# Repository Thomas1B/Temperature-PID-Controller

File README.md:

# Temperature PID Controller using an Arduino

This project uses a PID controller algorithm to heat up a heating cartridge and maintain an accurate temperature using an Arduino nano.
<br><br>

<br>

## Schematic

<br>

## Parts List

See `Parts_list.csv`

## Controls

1. Single-press to reset set temperature.
2. Double-press increase increment step for changing set temperature.
3. Press & hold to start up heating process.

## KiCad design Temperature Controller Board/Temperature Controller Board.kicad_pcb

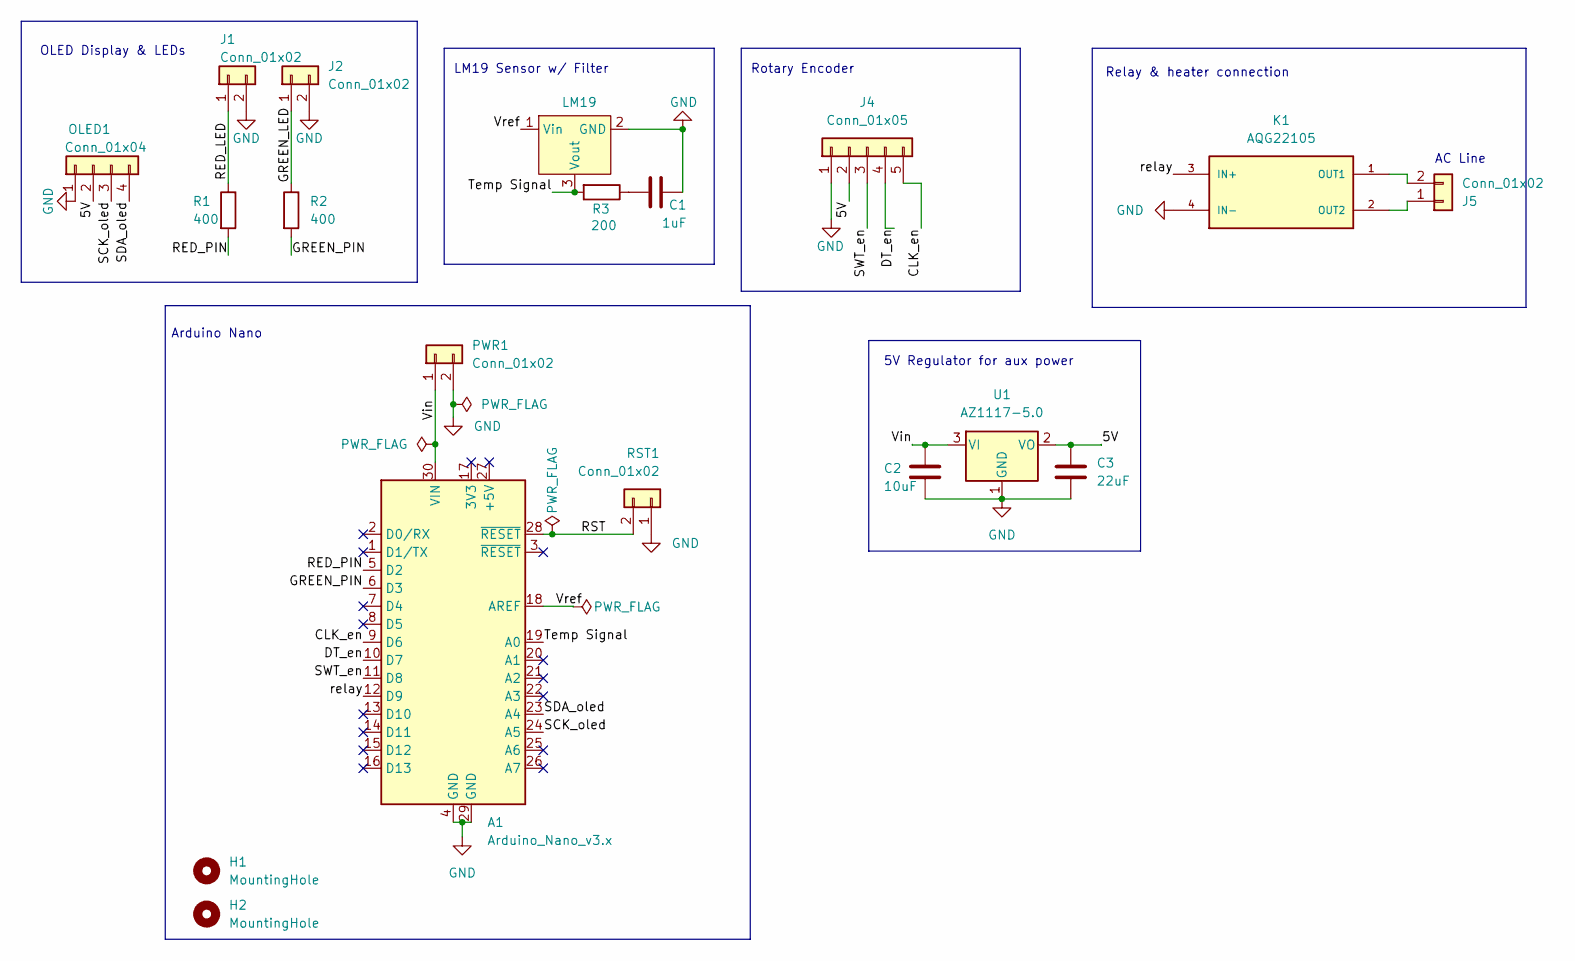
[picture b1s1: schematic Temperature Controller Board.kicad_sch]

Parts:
A1: Arduino_Nano_v3.x; Arduino Riser
C1: 1uF; C_0805_2012Metric_Pad1.18x1.45mm_HandSolder
C2: 10uF; C_0805_2012Metric_Pad1.18x1.45mm_HandSolder
C3: 22uF; C_0805_2012Metric_Pad1.18x1.45mm_HandSolder
H1, H2: MountingHole; MountingHole_3.2mm_M3
J1, J2: Conn_01x02; JST_XH_B2B-XH-A_1x02_P2.50mm_Vertical
J4: Conn_01x05; JST_XH_B5B-XH-A_1x05_P2.50mm_Vertical
J5: Conn_01x02; myTerminalBlock-2_P5.08mm
K1: AQG22105; RELAY_AQG22105
LM19: LM19; JST_XH_B3B-XH-AM_1x03_P2.50mm_Vertical
OLED1: Conn_01x04; JST_XH_B4B-XH-A_1x04_P2.50mm_Vertical
PWR1: Conn_01x02; JST_XH_B2B-XH-A_1x02_P2.50mm_Vertical
R1, R2: 400; R_0805_2012Metric_Pad1.20x1.40mm_HandSolder
R3: 200; R_0805_2012Metric_Pad1.20x1.40mm_HandSolder
RST1: Conn_01x02; JST_XH_B2B-XH-A_1x02_P2.50mm_Vertical
U1: AZ1117-5.0; SOT-223-3_TabPin2

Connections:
/5V: C3.1, J4.2, OLED1.2, U1.2 (VO)
/CLK_en: A1.9 (D6), J4.5
/DT_en: A1.10 (D7), J4.4
/GREEN_LED: J2.1, R2.1
/GREEN_PIN: A1.6 (D3), R2.2
/RED_LED: J1.1, R1.1
/RED_PIN: A1.5 (D2), R1.2
/RST: A1.28 (~RESET), RST1.2
/SCK_oled: A1.24 (A5), OLED1.3
/SDA_oled: A1.23 (A4), OLED1.4
/SWT_en: A1.11 (D8), J4.3
/Temp Signal: A1.19 (A0), LM19.3 (Vout), R3.2
/Vin: A1.30 (VIN), C2.1, PWR1.1, U1.3 (VI)
/Vref: A1.18 (AREF), LM19.1 (Vin)
/relay: A1.12 (D9), K1.3 (IN+)
GND: A1.4 (GND), A1.29 (GND), C1.1, C2.2, C3.2, J1.2, J2.2, J4.1, K1.4 (IN-), LM19.2 (GND), OLED1.1, PWR1.2, RST1.1, U1.1 (GND)
unnamed: C1.2, R3.1
unnamed: J5.1, K1.2 (OUT2)
unnamed: J5.2, K1.1 (OUT1)

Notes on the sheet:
Arduino Nano
5V Regulator for aux power
OLED Display & LEDs
AC Line
Rotary Encoder
Relay & heater connection
LM19 Sensor w/ Filter

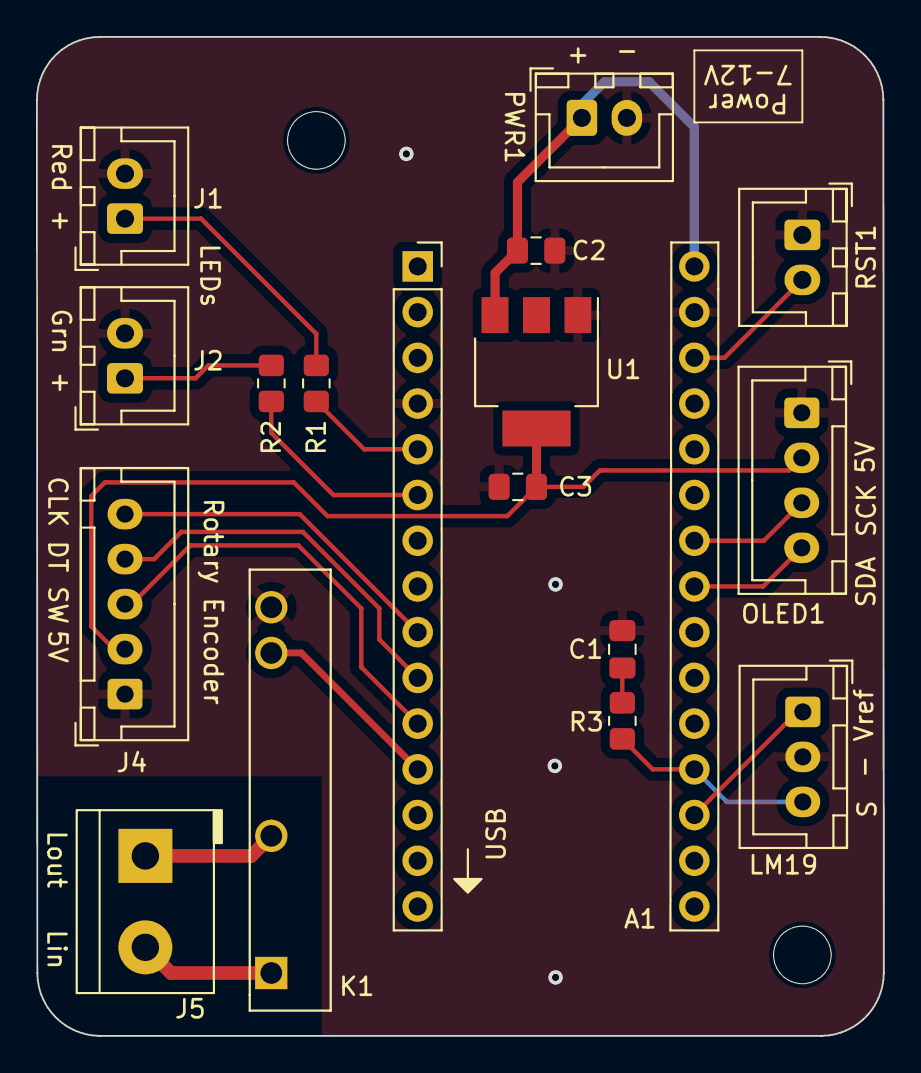
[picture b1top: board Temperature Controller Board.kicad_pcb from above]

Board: 2 copper layers, 47.1 x 55.5 mm, 19 parts (0 on the bottom side), 19 nets.

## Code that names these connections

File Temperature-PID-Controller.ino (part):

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BfButton btn(BfButton::STANDALONE_DIGITAL, SW, true, LOW);  // defining Encoder button object

// pins for LEDs
#define RED_LED 2
#define GREEN_LED 3

#define relay_pin 9  // Relay pin

#define LM19_pin A7  // Reference voltage pin

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  pinMode(CLK, INPUT);  // Encoder
  pinMode(DT, INPUT);
  pinMode(SW, INPUT_PULLUP);
  pinMode(relay_pin, OUTPUT);

  pinMode(LM19_pin, INPUT);  // LM19 Temp Sensor

  pinMode(RED_LED, OUTPUT);  // LEDs
  pinMode(GREEN_LED, OUTPUT);

  btn.onPress(read_encoder_btn)               // single click
    .onDoublePress(read_encoder_btn)          // double click
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  */

  if (state) {
    digitalWrite(relay_pin, HIGH);
  } else {
    digitalWrite(relay_pin, LOW);
  }
}

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
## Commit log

2023-02-05 need to add LCD to interface
2023-02-05 updated read
2023-02-05 change LED function
2023-02-05 Still need to add LCD
2023-02-05 added PID library
2023-02-05 fixed encoder error
2023-02-05 SAFE SPOT, need to add LCD and PID control
2023-02-05 testgin
2023-02-05 deleting testing
2023-02-05 image for readme
2023-02-10 an code for LCD Screen
2023-02-10 renamed file
2023-02-10 make code more efficient
2023-02-11 fixed temperature range
2023-02-11 formatted code
2023-02-11 updated intro
2023-02-11 added comments
2023-02-11 change code for encoder, trying to fix debouncing
2023-02-11 fixed debouncing
2023-02-21 added double press for larger increments
2023-02-21 added Kicad File
2023-02-21 updated comments
2023-03-23 testing ad590 sensor
2023-03-23 updating circuits
2023-03-23 syncing
2023-06-22 testing new Temp Sensor, LM19
2023-06-22 removed testing old sensor
2023-06-23 formatted
2023-07-06 testing OLED Screen
2023-07-07 Create LICENSE
2023-07-07 added OLED and LM19 Sensor
2023-07-07 updated OLED display
2023-07-10 removed old code
2023-07-28 updated code and schematic
2023-07-28 removed old schematic
2023-08-29 added 3d models and images
2023-08-29 updated testing
2023-08-29 updated Schematic and PCB
2023-08-29 removed old files
2023-09-01 updated program code
2023-09-01 added Parts List
2023-09-01 'syncing
2023-09-02 added PID code
